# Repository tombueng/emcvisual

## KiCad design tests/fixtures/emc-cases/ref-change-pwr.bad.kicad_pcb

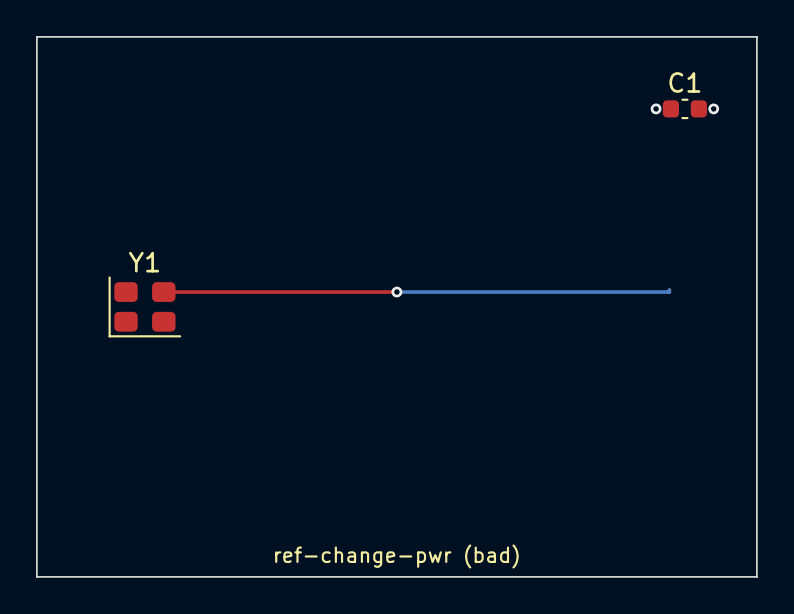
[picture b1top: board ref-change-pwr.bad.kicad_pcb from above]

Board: 4 copper layers, 40.0 x 30.0 mm, 3 parts (1 on the bottom side), 3 nets.

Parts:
C1: 100nF; C_0603_1608Metric
U1: 74LVC1G04; SOT-23-5
Y1: 25MHz; Oscillator_SMD_Abracon_ASE-4Pin_3.2x2.5mm

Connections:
+3V3: C1.1, U1.5, Y1.1, Y1.4
CLK: U1.1, Y1.3
GND: C1.2, U1.2, Y1.2

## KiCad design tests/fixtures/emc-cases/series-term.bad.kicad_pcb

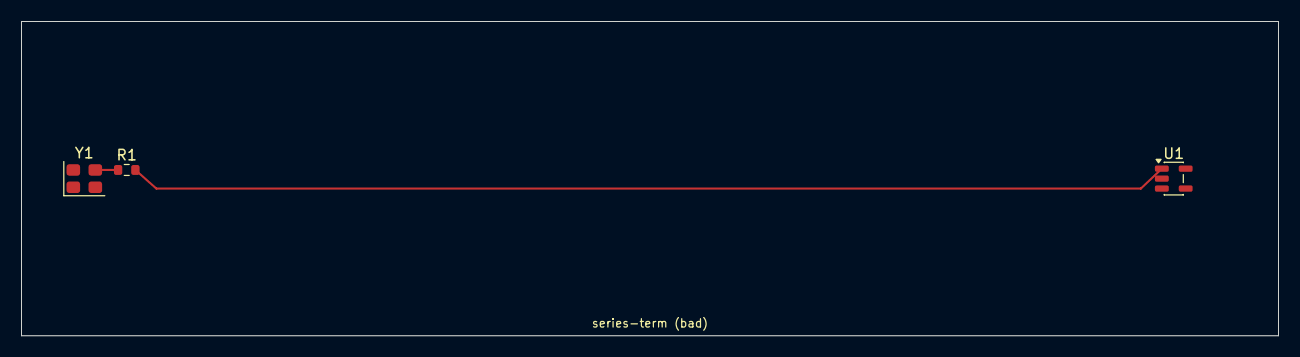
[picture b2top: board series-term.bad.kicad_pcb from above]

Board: 2 copper layers, 120.0 x 30.0 mm, 3 parts (0 on the bottom side), 4 nets.

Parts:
R1: 0R; R_0603_1608Metric
U1: 74LVC1G04; SOT-23-5
Y1: 25MHz; Oscillator_SMD_Abracon_ASE-4Pin_3.2x2.5mm

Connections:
+3V3: U1.5, Y1.1, Y1.4
CLK: R1.2, U1.1
CLK_SRC: R1.1, Y1.3
GND: U1.2, Y1.2
